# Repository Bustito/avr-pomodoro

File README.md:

# avr-pomodoro
Hello, this is a personal repository about a little gadget I came up with. It's a pomodoro timer using an atmega328p, and i'm looking forward to use a attiny device.

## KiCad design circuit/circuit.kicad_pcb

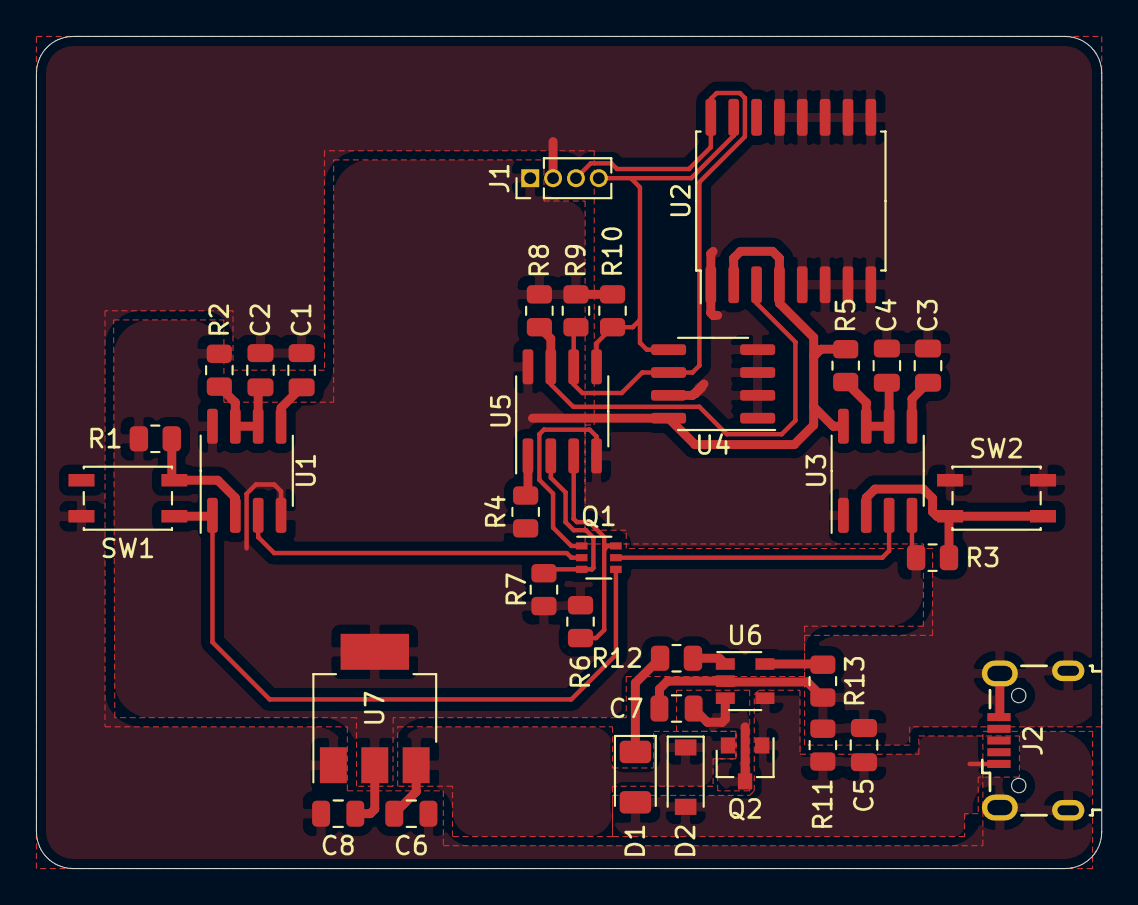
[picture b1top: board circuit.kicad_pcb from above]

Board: 2 copper layers, 59.2 x 46.2 mm, 36 parts (0 on the bottom side), 22 nets.

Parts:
C1, C3: 100nF; C_0805_2012Metric
C2, C4: 1uF; C_0805_2012Metric
C5, C6, C7, C8: 4.7uF; C_0805_2012Metric
D1: LED; LED_1206_3216Metric
D2: MBR0520; D_SOD-123
J1: Conn_01x04_MountingPin; PinHeader_1x04_P1.27mm_Vertical
J2: USB_B_Micro; USB_Micro-B_Wuerth_629105150521
Q1: FFB2222A; SOT-363_SC-70-6
Q2: BSS84; SOT-23
R1, R3, R4, R6, R7, R8, R9, R10: 10K; R_0805_2012Metric
R2, R5: 47K; R_0805_2012Metric
R11: 100K; R_0805_2012Metric
R12: 470; R_0805_2012Metric
R13: 2K; R_0805_2012Metric
SW1, SW2: SW_Push; SW_SPST_EVQP2
U1, U3: TLC555xD; SOIC-8_3.9x4.9mm_P1.27mm
U2: DS3231M; SOIC-16W_7.5x10.3mm_P1.27mm
U4: 24LC02; SOIC-8_3.9x4.9mm_P1.27mm
U5: ATtiny25-20SSU; SOIC-8_3.9x4.9mm_P1.27mm
U6: MCP73831-2-OT; SOT-23-5
U7: LT1117-3.3; SOT-223-3_TabPin2

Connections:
+3V3: C8.2, J1.1, R1.1, R2.1, R3.1, R4.1, R5.1, R6.1, R7.1, R8.1, R9.1, R10.1, U1.4, U1.8, U2.2, U2.4, U3.4, U3.8, U4.8, U5.8, U7.2
+5V: C5.2, D1.2, D2.2, J2.1, Q2.1, R11.1, U6.4
ALARM: R8.2, U2.3, U5.7
BATT: C7.2, Q2.3, U6.3
GND: C1.2, C2.2, C3.2, C4.2, C5.1, C6.1, C7.1, C8.1, J1.2, J2.5, J2.6, Q1.1, Q1.4, R11.2, R13.1, SW1.1, SW2.1, U1.1, U2.1, U2.5, U2.6, U2.7, U2.8, U2.9, U2.10, U2.11, U2.12, U2.13, U3.1, U4.1, U4.2, U4.3, U4.4, U4.7, U5.4, U6.2, U7.1
unnamed: C1.1, U1.5
unnamed: C2.1, R2.2, U1.6, U1.7
unnamed: C3.1, U3.5
unnamed: C4.1, R5.2, U3.6, U3.7
unnamed: D1.1, R12.1
unnamed: Q1.2, U1.3
unnamed: Q1.5, U3.3
unnamed: R1.2, SW1.2, U1.2
unnamed: R3.2, SW2.2, U3.2
unnamed: R13.2, U6.5
PINA: Q1.3, R7.2, U5.2
PINB: Q1.6, R6.2, U5.3
RESET: R4.2, U5.1
SCL: J1.3, R9.2, U2.16, U4.6, U5.6
SDA: J1.4, R10.2, U2.15, U4.5, U5.5
STAT: R12.2, U6.1
VCC: C6.2, D2.1, Q2.2, U7.3

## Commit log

2021-08-12 Project started
2021-08-12 Added the timer and serial communication funtions
2021-08-12 Optimized the interrupt use
2021-08-13 Added menu logic
2021-08-13 Menu functions well now
2021-08-13 Added pomodoro, and move conditionals to the external interrupts ISRs
2021-08-14 14/8/21
